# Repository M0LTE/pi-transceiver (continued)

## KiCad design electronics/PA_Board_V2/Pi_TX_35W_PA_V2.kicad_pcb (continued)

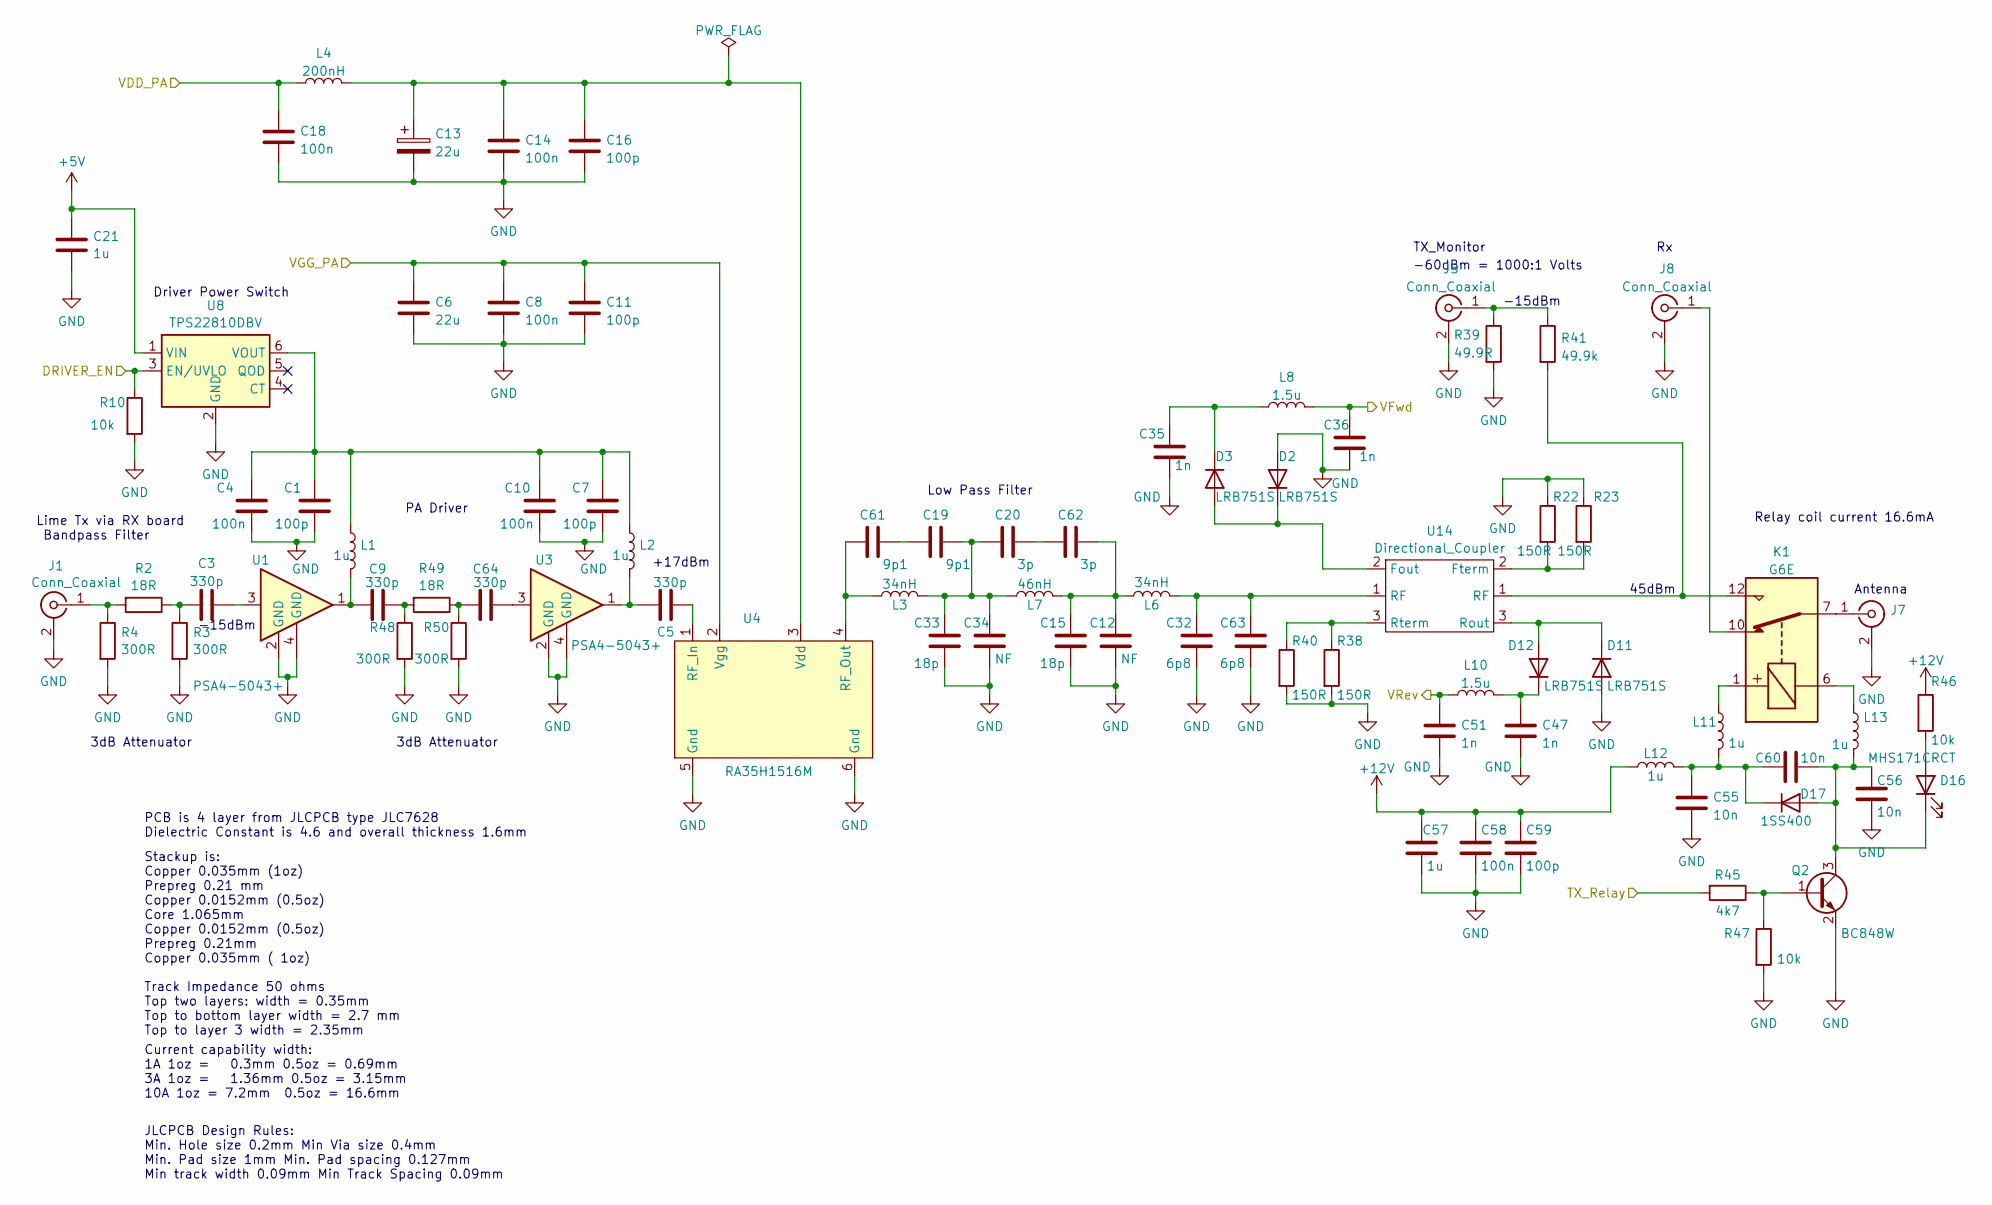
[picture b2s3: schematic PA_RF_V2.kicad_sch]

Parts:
C1, C7, C11, C16, C59: 100p; C_0603_1608Metric; LCSC Part C296046
C3, C5, C9, C64: 330p; C_0603_1608Metric; LCSC Part C458903
C4, C8, C10, C14, C18, C58: 100n; C_0603_1608Metric; LCSC Part C88136
C6: 22u; C_0805_2012Metric; LCSC Part C602037
C12, C34: NF; C_1206_3216Metric
C13: 22u; CP_EIA-7343-43_Kemet-X; LCSC Part C1956447
C15, C33: 18p; C_1206_3216Metric
C19, C61: 9p1; C_1206_3216Metric
C20, C62: 3p; C_1206_3216Metric
C21: 1u; C_0603_1608Metric; LCSC Part C88136
C32, C63: 6p8; C_1206_3216Metric
C35, C36, C47, C51: 1n; C_0603_1608Metric; LCSC Part C2839443
C55, C56, C60: 10n; C_0603_1608Metric; LCSC Part C2215227
C57: 1u; C_0603_1608Metric; LCSC Part C89376
D2, D3, D11, D12: LRB751S; D_SOD-523; LCSC Part C113407
D16: MHS171CRCT; MHS171; LCSC Part C693903
D17: 1SS400; D_SOD-523; LCSC Part C68951
J1, J5, J7, J8: Conn_Coaxial; SMA_Samtec_SMA-J-P-X-ST-EM1_EdgeMount; LCSC Part C496550
K1: G6E; Relay_SPDT_Omron_G6E; LCSC Part C1525391
L1, L2, L11, L12, L13: 1u; L_0805_2012Metric; LCSC Part C703134
L3, L6: 34nH; Wire_Inductor 12x8.5
L4: 200nH; L_1812_4532Metric; LCSC Part C2858475
L7: 46nH; Wire_Inductor 15.5x8.5
L8, L10: 1.5u; L_0805_2012Metric; LCSC Part C139220
Q2: BC848W; SOT-323_SC-70; LCSC Part C549496
R2, R49: 18R; R_0603_1608Metric; LCSC Part C245924
R3, R4, R48, R50: 300R; R_0603_1608Metric; LCSC Part C2930092
R10, R46, R47: 10k; R_0603_1608Metric; LCSC Part C25804
R22, R23, R38, R40: 150R; R_0603_1608Metric; LCSC Part C22808
R39: 49.9R; R_0603_1608Metric; LCSC Part C23185
R41: 49.9k; R_0603_1608Metric; LCSC Part C23184
R45: 4k7; R_0603_1608Metric; LCSC Part C23162
U1, U3: PSA4-5043+; SOT-343_SC-70-4; LCSC Part C5240848
U4: RA35H1516M; RF_PA_Module
U8: TPS22810DBV; SOT-23-6; LCSC Part C205990
U14: Directional_Coupler; Linear_Coupler

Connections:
+5V: C21.1, U8.1 (VIN); also elsewhere on the board
+12V: C57.1, C58.1, C59.1, L12.1, R46.1; also elsewhere on the board
/PA_Power/VDD_PA: C18.1, L4.1; also elsewhere on the board
/PA_Power/VGG_PA: C6.1, C8.1, C11.1, U4.2 (Vgg); also elsewhere on the board
/PA_Protection/DRIVER_EN: R10.1, U8.3 (EN/UVLO); also elsewhere on the board
/PA_Protection/TX_Relay: R45.2; also elsewhere on the board
/PA_Protection/VFwd: C36.1, L8.2; also elsewhere on the board
/PA_Protection/VRev: C51.1, L10.1; also elsewhere on the board
GND: C1.1, C4.1, C6.2, C7.1, C8.2, C10.1, C11.2, C12.2, C13.2, C14.2, C15.2, C16.2, C18.2, C21.2, C32.2, C33.2, C34.2, C35.2, C36.2, C47.2, C51.2, C55.2, C56.2, C57.2, C58.2, C59.2, C63.2, D2.2 (A), D11.2 (A), J1.2 (Ext), J5.2 (Ext), J7.2 (Ext), J8.2 (Ext), Q2.2 (E), R3.2, R4.2, R10.2, R22.1, R23.1, R38.2, R39.2, R40.2, R47.2, R48.2, R50.2, U1.2 (GND), U1.4 (GND), U3.2 (GND), U3.4 (GND), U4.5 (Gnd), U4.6 (Gnd), U8.2 (GND); also elsewhere on the board
unnamed: C3.1, U1.3
unnamed: C3.2, R2.1, R3.1
unnamed: C5.2, L2.2, U3.1
unnamed: C9.1, R48.1, R49.2
unnamed: C9.2, L1.2, U1.1
unnamed: C12.1, C15.1, C62.2, L6.1, L7.2
unnamed: C19.1, C61.2
unnamed: C19.2, C20.1, C33.1, C34.1, L3.2, L7.1
unnamed: C20.2, C62.1
unnamed: C64.1, U3.3
unnamed: C64.2, R49.1, R50.1
unnamed: C35.1, D3.1 (K), L8.1
unnamed: C47.1, D12.1 (K), L10.2
unnamed: D16.2 (A), R46.2
unnamed: C56.1, C60.1, D16.1 (K), D17.2 (A), L13.2, Q2.3 (C)
unnamed: C55.1, C60.2, D17.1 (K), L11.2, L12.2
unnamed: J1.1 (In), R2.2, R4.1
unnamed: J5.1 (In), R39.1, R41.1
unnamed: J7.1 (In), K1.7
unnamed: J8.1 (In), K1.10
unnamed: K1.1, L11.1
unnamed: K1.6, L13.1
unnamed: Q2.1 (B), R45.1, R47.1
unnamed: C5.1, U4.1 (RF_In)
unnamed: C61.1, L3.1, U4.4 (RF_Out)
unnamed: C13.1, C14.1, C16.1, L4.2, U4.3 (Vdd)
unnamed: C1.2, C4.2, C7.2, C10.2, L1.1, L2.1, U8.6 (VOUT)

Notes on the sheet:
3dB Attenuator
JLCPCB Design Rules: Min. Hole size 0.2mm Min Via size 0.4mm Min. Pad size 1mm Min. Pad spacing 0.127mm Min track width 0.09mm Min Track Spacing 0.09mm
Driver Power Switch
+17dBm
Stackup is: Copper 0.035mm (1oz) Prepreg 0.21 mm Copper 0.0152mm (0.5oz) Core 1.065mm Copper 0.0152mm (0.5oz) Prepreg 0.21mm Copper 0.035mm ( 1oz)
Current capability width: 1A 1oz = 0.3mm 0.5oz = 0.69mm 3A 1oz = 1.36mm 0.5oz = 3.15mm 10A 1oz = 7.2mm 0.5oz = 16.6mm
Antenna
TX_Monitor
45dBm
Lime Tx via RX board Bandpass Filter
-15dBm
Low Pass Filter
-60dBm = 1000:1 Volts
Track Impedance 50 ohms Top two layers: width = 0.35mm Top to bottom layer width = 2.7 mm Top to layer 3 width = 2.35mm
Relay coil current 16.6mA
PCB is 4 layer from JLCPCB type JLC7628 Dielectric Constant is 4.6 and overall thickness 1.6mm
PA Driver

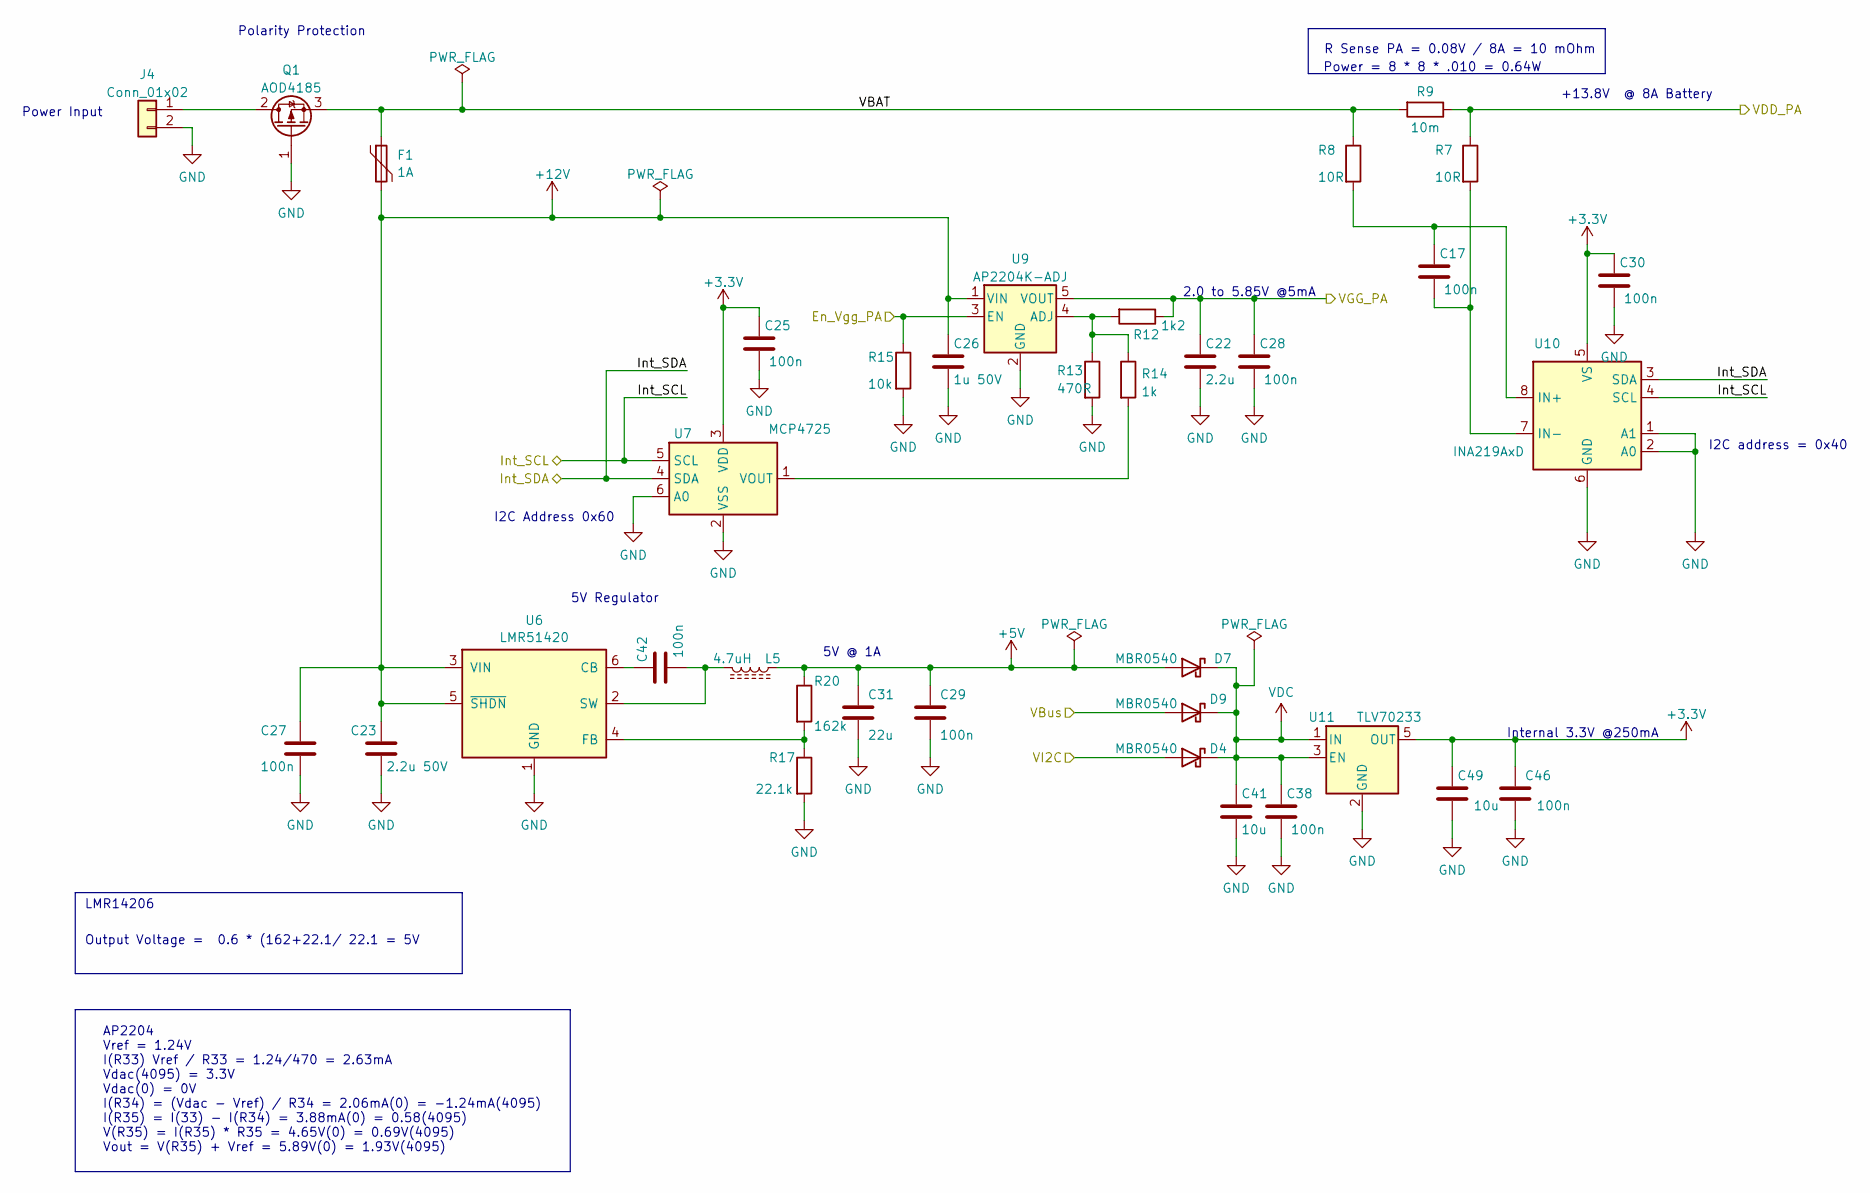
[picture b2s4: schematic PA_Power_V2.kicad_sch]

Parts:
C17, C25, C27, C28, C29, C30, C38, C42, C46: 100n; C_0603_1608Metric; LCSC Part C88136
C22: 2.2u; C_0603_1608Metric; LCSC Part C57895
C23: 2.2u 50V; C_0805_2012Metric; LCSC Part C377773
C26: 1u 50V; C_0603_1608Metric; LCSC Part C15849
C31: 22u; C_0805_2012Metric; LCSC Part C602037
C41, C49: 10u; C_0603_1608Metric; LCSC Part C96446
D4, D7, D9: MBR0540; D_SOD-123; LCSC Part C3018524
F1: 1A; Fuse_1206_3216Metric; LCSC Part C910830
J4: Conn_01x02; PhoenixContact_MSTBA_2,5_2-G_1x02_P5.00mm_Horizontal; LCSC Part C3697
L5: 4.7uH; L_7.3x7.3_H3.5; LCSC Part C76857
Q1: AOD4185; TO-252-2; LCSC Part C5261064
R7, R8: 10R; R_0603_1608Metric; LCSC Part C22859
R9: 10m; R_2816_7142Metric; LCSC Part C843884
R12: 1k2; R_0603_1608Metric; LCSC Part C22765
R13: 470R; R_0603_1608Metric; LCSC Part C23179
R14: 1k; R_0603_1608Metric; LCSC Part C21190
R15: 10k; R_0603_1608Metric; LCSC Part C25804
R17: 22.1k; R_0603_1608Metric; LCSC Part C25961
R20: 162k; R_0603_1608Metric; LCSC Part C3016073
U6: LMR51420; SOT-23-6; LCSC Part C5383002
U7: MCP4725; SOT-23-6; LCSC Part C144198
U9: AP2204K-ADJ; SOT-23-5; LCSC Part C264072
U10: INA219AxD; SOIC-8_3.9x4.9mm_P1.27mm; LCSC Part C138706
U11: TLV70233; SOT-23-5; LCSC Part C26833

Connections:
+3.3V: C25.1, C30.1, C46.1, C49.1, U7.3 (VDD), U10.5 (VS), U11.5 (OUT); also elsewhere on the board
+5V: C29.1, C31.1, D7.2 (A), L5.1, R20.1; also elsewhere on the board
+12V: C23.1, C26.1, C27.1, F1.2, U6.3 (VIN), U6.5 (~SHDN), U9.1 (VIN); also elsewhere on the board
/PA_Power/En_Vgg_PA: R15.1, U9.3 (EN); also elsewhere on the board
/PA_Power/Int_SCL: U7.5 (SCL), U10.4 (SCL); also elsewhere on the board
/PA_Power/Int_SDA: U7.4 (SDA), U10.3 (SDA); also elsewhere on the board
/PA_Power/VBAT: F1.1, Q1.3 (S), R8.1, R9.2
/PA_Power/VBus: D9.2 (A); also elsewhere on the board
/PA_Power/VDD_PA: R7.1, R9.1; also elsewhere on the board
/PA_Power/VGG_PA: C22.1, C28.1, R12.1, U9.5 (VOUT); also elsewhere on the board
/PA_Power/VI2C: D4.2 (A); also elsewhere on the board
GND: C22.2, C23.2, C25.2, C26.2, C27.2, C28.2, C29.2, C30.2, C31.2, C38.2, C41.2, C46.2, C49.2, J4.2, Q1.1 (G), R13.2, R15.2, R17.2, U6.1 (GND), U7.2 (VSS), U7.6 (A0), U9.2 (GND), U10.1 (A1), U10.2 (A0), U10.6 (GND), U11.2 (GND); also elsewhere on the board
unnamed: J4.1, Q1.2 (D)
unnamed: C42.1, U6.6 (CB)
unnamed: R17.1, R20.2, U6.4 (FB)
unnamed: C42.2, L5.2, U6.2 (SW)
unnamed: R14.2, U7.1 (VOUT)
unnamed: R12.2, R13.1, R14.1, U9.4 (ADJ)
unnamed: C17.1, R8.2, U10.8 (IN+)
unnamed: C17.2, R7.2, U10.7 (IN-)
VDC: C38.1, C41.1, D4.1 (K), D7.1 (K), D9.1 (K), U11.1 (IN), U11.3 (EN); also elsewhere on the board

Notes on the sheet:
5V @ 1A
Power Input
2.0 to 5.85V @5mA
I2C Address 0x60
+13.8V @ 8A Battery
I2C address = 0x40
LMR14206
Internal 3.3V @250mA
AP2204 Vref = 1.24V I(R33) Vref / R33 = 1.24/470 = 2.63mA Vdac(4095) = 3.3V Vdac(0) = 0V I(R34) = (Vdac - Vref) / R34 = 2.06mA(0) = -1.24mA(4095) I(R35) = I(33) - I(R34) = 3.88mA(0) = 0.58(4095) V(R35) = I(R35) * R35 = 4.65V(0) = 0.69V(4095) Vout = V(R35) + Vref = 5.89V(0) = 1.93V(4095)
R Sense PA = 0.08V / 8A = 10 mOhm
Polarity Protection
Power = 8 * 8 * .010 = 0.64W
Output Voltage = 0.6 * (162+22.1/ 22.1 = 5V
5V Regulator

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
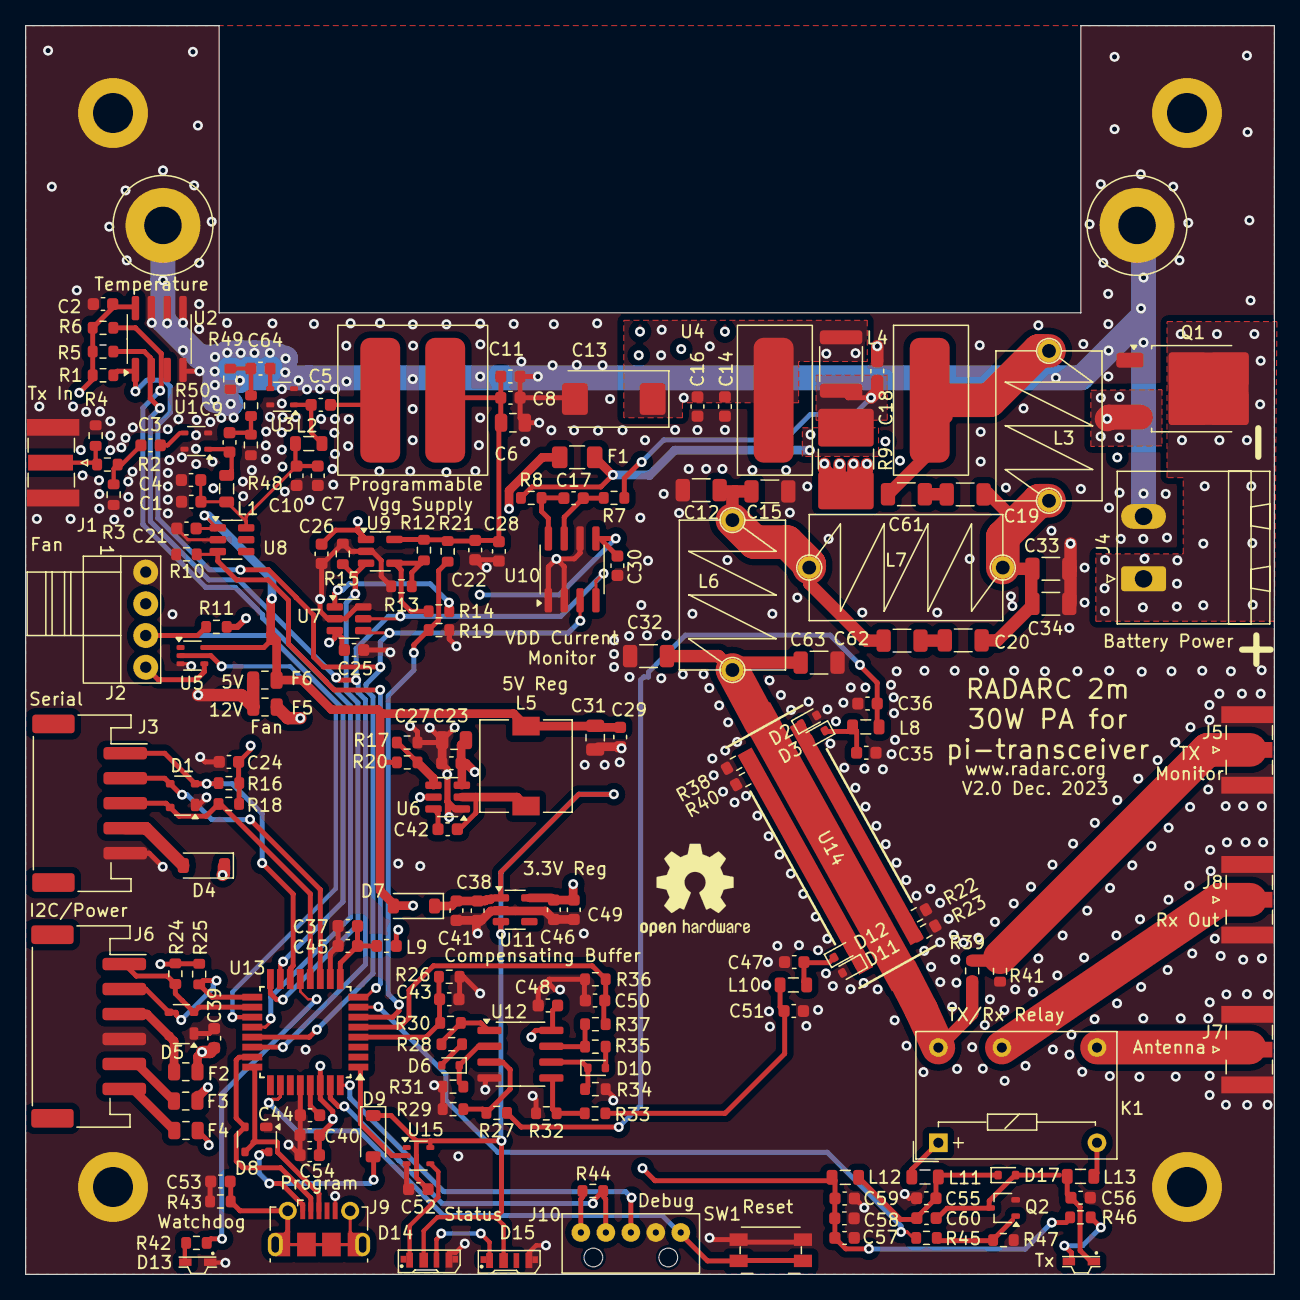
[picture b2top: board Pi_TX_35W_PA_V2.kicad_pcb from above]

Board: 4 copper layers, 100.0 x 100.0 mm, 185 parts (1 on the bottom side), 95 nets.

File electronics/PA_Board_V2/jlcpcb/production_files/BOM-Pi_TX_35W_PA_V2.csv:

Comment,Designator,Footprint,LCSC
LRB751S,"D11,D12,D2,D3",D_SOD-523,C113407
USB_B_Micro,J9,USB_Micro-B_Molex-105017-0001,C136000
INA219AxD,U10,SOIC-8_3.9x4.9mm_P1.27mm,C138706
1.5u,"L10,L8",L_0805_2012Metric,C139220
MCP4725,U7,SOT-23-6,C144198
G6E,K1,Relay_SPDT_Omron_G6E,C1525391
1u 50V,C26,C_0603_1608Metric,C15849
22u,C13,CP_EIA-7343-43_Kemet-X,C1956447
TPS22810DBV,U8,SOT-23-6,C205990
1k,"R14,R42,R44",R_0603_1608Metric,C21190
10n,"C55,C56,C60",C_0603_1608Metric,C2215227
1k2,R12,R_0603_1608Metric,C22765
150R,"R22,R23,R38,R40",R_0603_1608Metric,C22808
10R,"R7,R8",R_0603_1608Metric,C22859
1M,R43,R_0603_1608Metric,C22935
330R,"R30,R37",R_0603_1608Metric,C23138
4k7,"R1,R16,R18,R24,R25,R28,R35,R45,R5,R6",R_0603_1608Metric,C23162
470R,R13,R_0603_1608Metric,C23179
49.9k,R41,R_0603_1608Metric,C23184
49.9R,R39,R_0603_1608Metric,C23185
18R,"R2,R49",R_0603_1608Metric,C245924
100k,"R29,R31,R32,R34",R_0603_1608Metric,C25803
10k,"R10,R11,R15,R19,R26,R27,R33,R36,R46,R47",R_0603_1608Metric,C25804
47k,R21,R_0603_1608Metric,C25819
22.1k,R17,R_0603_1608Metric,C25961
AP2204K-ADJ,U9,SOT-23-5,C264072
SP0503BAHT,"D1,D5,D8",SOT-143,C2682275
TLV70233,U11,SOT-23-5,C26833
1n,"C35,C36,C43,C47,C50,C51",C_0603_1608Metric,C2839443
150mA,"F2,F3,F4",Fuse_0805_2012Metric,C2840556
200nH,L4,L_1812_4532Metric,C2858475
SK6812,"D14,D15",SK6812SIDE-A-RVS,C2890037
300R,"R3,R4,R48,R50",R_0603_1608Metric,C2930092
LM2904,U12,SOIC-8_3.9x4.9mm_P1.27mm,C2941725
100p,"C1,C11,C16,C59,C7",C_0603_1608Metric,C296046
162k,R20,R_0603_1608Metric,C3016073
MBR0540,"D4,D7,D9",D_SOD-123,C3018524
2.2u 50V,C23,C_0805_2012Metric,C377773
330p,"C3,C5,C64,C9",C_0603_1608Metric,C458903
Conn_Coaxial,"J1,J5,J7,J8",SMA_Samtec_SMA-J-P-X-ST-EM1_EdgeMount,C496550
74LV1T34,"U15,U5",SOT-353_SC-70-5,C5199768
PSA4-5043+,"U1,U3",MM1362 PSA4-5043+,C5240848
AOD4185,Q1,TO-252-2,C5261064
SW_Push,SW1,Panasonic_EVQPUK_EVQPUB,C526225
LMR51420,U6,SOT-23-6,C5383002
BC848W,Q2,SOT-323_SC-70,C549496
4n7,C53,C_0603_1608Metric,C576815
2.2u,C22,C_0603_1608Metric,C57895
22u,"C31,C6",C_0805_2012Metric,C602037
ATSAMD21E18A-A,U13,TQFP-32_7x7mm_P0.8mm,C618770
1SS400,"D10,D17,D6",D_SOD-523,C68951
MHS171CRCT,D16,MHS171,C693903
MHS171UBCT,D13,MHS171,C693906
1u,"L1,L11,L12,L13,L2",L_0805_2012Metric,C703134
LM75B,U2,SOIC-8_3.9x4.9mm_P1.27mm,C725792
Conn_01x05,J3,JST_PH_S5B-PH-SM4-TB_1x05-1MP_P2.00mm_Horizontal,C7429692
Conn_01x06,J6,JST_PH_S6B-PH-SM4-TB_1x06-1MP_P2.00mm_Horizontal,C7429693
4.7uH,L5,L_7.3x7.3_H3.5,C76857
10m,R9,R_2816_7142Metric,C843884
100n,"C10,C14,C17,C18,C2,C21,C24,C25,C27,C28,C29,C30,C38,C39,C4,C42,C45,C46,C48,C54,C58,C8",C_0603_1608Metric,C88136
1u,"C37,C40,C44,C52,C57",C_0603_1608Metric,C89376
1A,F1,Fuse_1206_3216Metric,C910830
10u,"C41,C49",C_0603_1608Metric,C96446
L_Ferrite,L9,L_0603_1608Metric,C98298

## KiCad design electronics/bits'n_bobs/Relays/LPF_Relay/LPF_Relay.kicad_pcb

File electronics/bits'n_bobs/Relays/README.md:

# Relays

A selection of Relay modules to test different options for the Tx/Rx relay for the Pi Transceiver

Relay Options are:

* G2RL Large through hole relay recommended by W6PQL
* HF3 Surface mount relay recommended by W6PQL
* EE2 Surface mount relay used in Lime RFE and IC-9700
* G6E Through hole relay used in Elecraft XV144

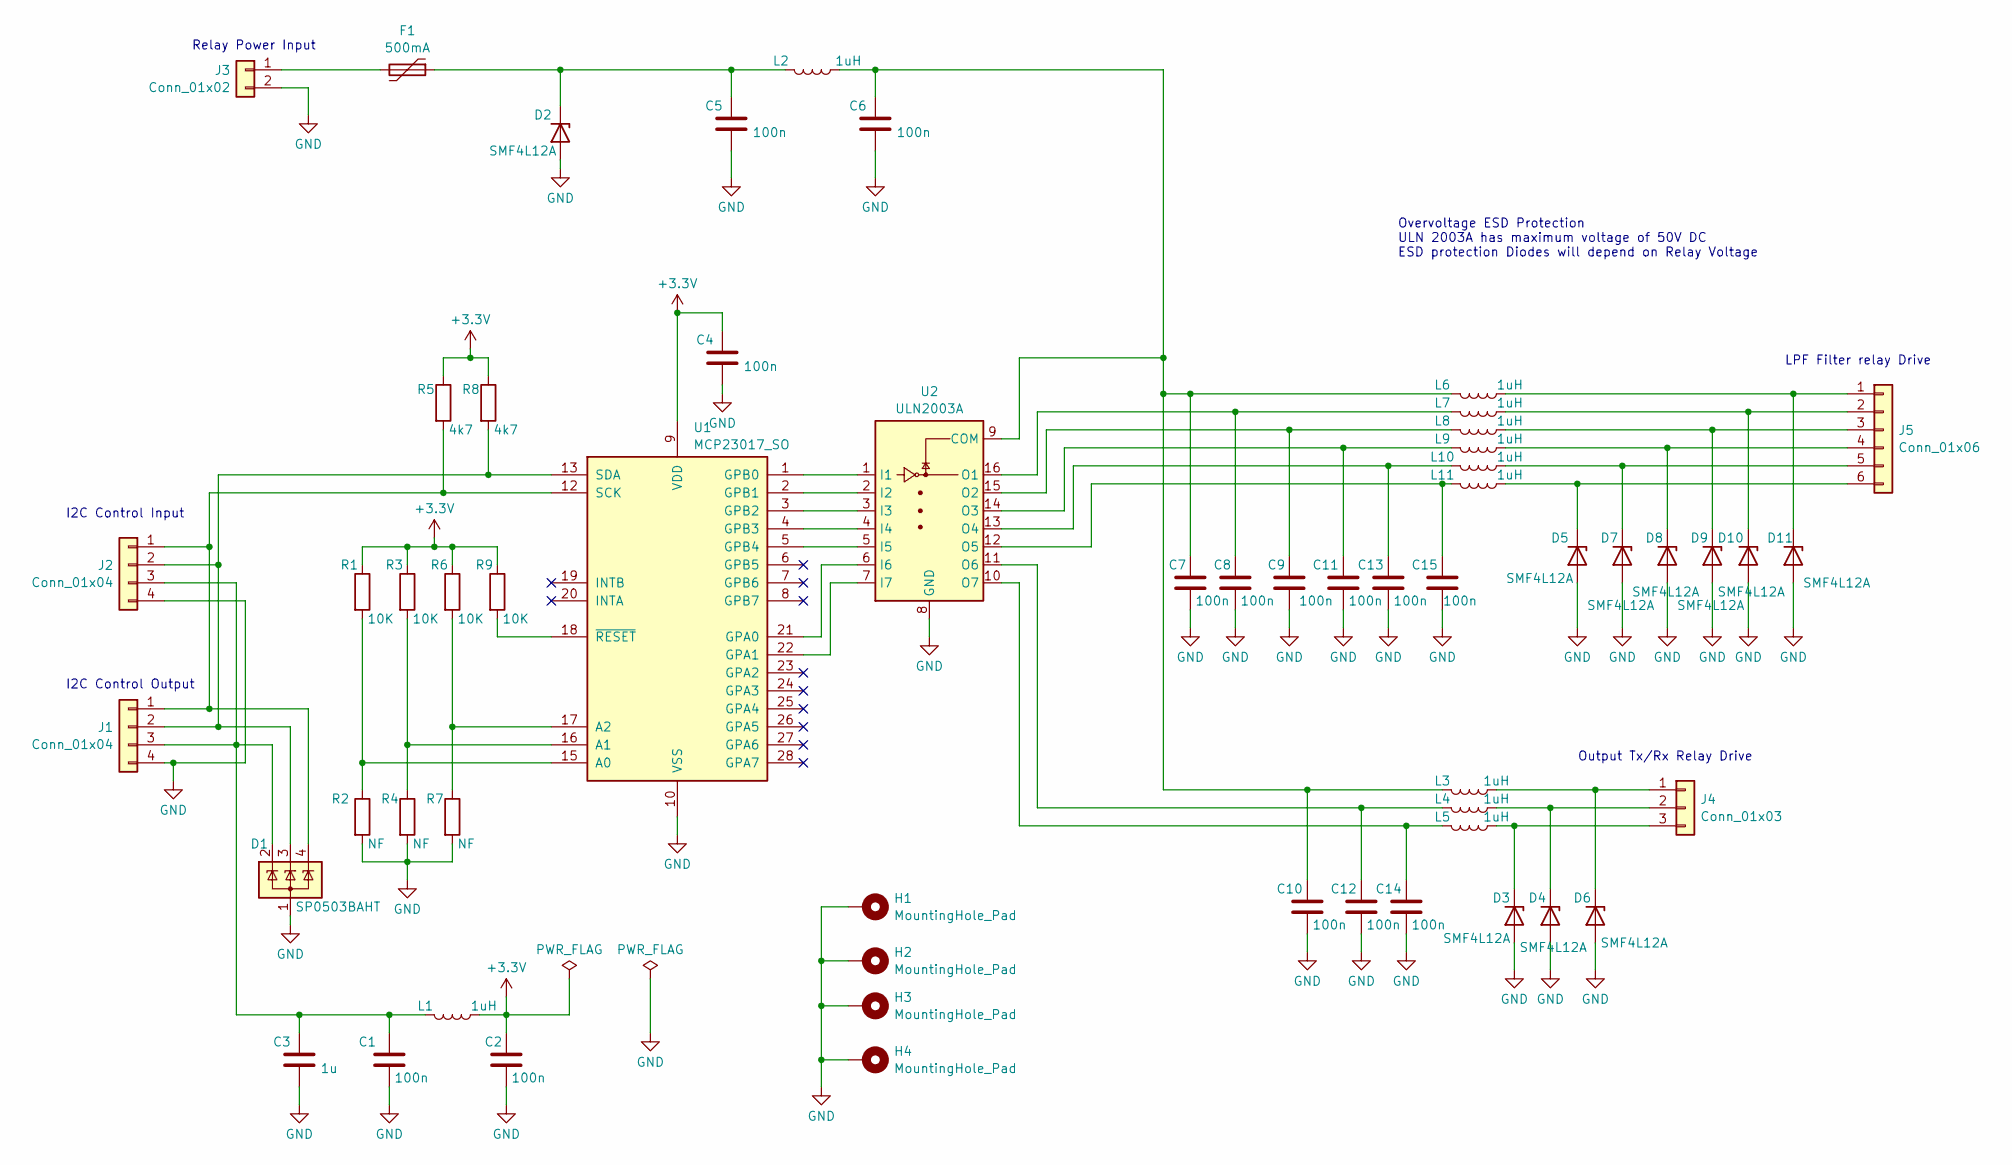
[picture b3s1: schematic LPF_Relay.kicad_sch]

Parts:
C1, C2, C4, C5, C6, C7, C8, C9, C10, C11, C12, C13, C14, C15: 100n; C_0603_1608Metric
C3: 1u; C_0603_1608Metric
D1: SP0503BAHT; SOT-143
D2, D3, D4, D5, D6, D7, D8, D9, D10, D11: SMF4L12A; D_SOD-123F
F1: 500mA; Fuse_Bourns_MF-SM_9.5x6.71mm
H1, H2, H3, H4: MountingHole_Pad; MountingHole_3.2mm_M3_DIN965_Pad
J1, J2: Conn_01x04; JST_PH_S4B-PH-SM4-TB_1x04-1MP_P2.00mm_Horizontal
J3: Conn_01x02; JST_XH_S2B-XH-A-1_1x02_P2.50mm_Horizontal
J4: Conn_01x03; JST_XH_S3B-XH-A-1_1x03_P2.50mm_Horizontal
J5: Conn_01x06; JST_XH_S6B-XH-A-1_1x06_P2.50mm_Horizontal
L1, L2, L3, L4, L5, L6, L7, L8, L9, L10, L11: 1uH; L_0603_1608Metric
R1, R3, R6, R9: 10K; R_0603_1608Metric
R2, R4, R7: NF; R_0603_1608Metric
R5, R8: 4k7; R_0603_1608Metric
U1: MCP23017_SO; SSOP-28_5.3x10.2mm_P0.65mm
U2: ULN2003A; SO-16_3.9x9.9mm_P1.27mm

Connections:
+3.3V: C2.1, C4.1, L1.1, R1.1, R3.1, R5.1, R6.1, R8.1, R9.1, U1.9 (VDD)
GND: C1.2, C2.2, C3.2, C4.2, C5.2, C6.2, C7.2, C8.2, C9.2, C10.2, C11.2, C12.2, C13.2, C14.2, C15.2, D1.1 (A), D2.2 (A), D3.2 (A), D4.2 (A), D5.2 (A), D6.2 (A), D7.2 (A), D8.2 (A), D9.2 (A), D10.2 (A), D11.2 (A), H1.1, H2.1, H3.1, H4.1, J1.4, J2.4, J3.2, R2.2, R4.2, R7.2, U1.10 (VSS), U2.8 (GND)
unnamed: C5.1, D2.1 (K), F1.1, L2.2
unnamed: D3.1 (K), J4.3, L5.1
unnamed: D4.1 (K), J4.2, L4.1
unnamed: D5.1 (K), J5.6, L11.1
unnamed: D6.1 (K), J4.1, L3.1
unnamed: D7.1 (K), J5.5, L10.1
unnamed: D8.1 (K), J5.4, L9.1
unnamed: D9.1 (K), J5.3, L8.1
unnamed: D10.1 (K), J5.2, L7.1
unnamed: D11.1 (K), J5.1, L6.1
unnamed: D1.4 (K), J1.1, J2.1, R5.2, U1.12 (SCK)
unnamed: D1.3 (K), J1.2, J2.2, R8.2, U1.13 (SDA)
unnamed: C1.1, C3.1, D1.2 (K), J1.3, J2.3, L1.2
unnamed: F1.2, J3.1
unnamed: R1.2, R2.1, U1.15 (A0)
unnamed: R3.2, R4.1, U1.16 (A1)
unnamed: R6.2, R7.1, U1.17 (A2)
unnamed: U1.21 (GPA0), U2.6 (I6)
unnamed: U1.22 (GPA1), U2.7 (I7)
unnamed: U1.1 (GPB0), U2.1 (I1)
unnamed: U1.2 (GPB1), U2.2 (I2)
unnamed: U1.3 (GPB2), U2.3 (I3)
unnamed: U1.4 (GPB3), U2.4 (I4)
unnamed: U1.5 (GPB4), U2.5 (I5)
unnamed: R9.2, U1.18 (~RESET)
unnamed: C6.1, C7.1, C10.1, L2.1, L3.2, L6.2, U2.9 (COM)
unnamed: C8.1, L7.2, U2.16 (O1)
unnamed: C9.1, L8.2, U2.15 (O2)
unnamed: C11.1, L9.2, U2.14 (O3)
unnamed: C13.1, L10.2, U2.13 (O4)
unnamed: C15.1, L11.2, U2.12 (O5)
unnamed: C12.1, L4.2, U2.11 (O6)
unnamed: C14.1, L5.2, U2.10 (O7)

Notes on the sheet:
I2C Control Output
LPF Filter relay Drive
Output Tx/Rx Relay Drive
I2C Control Input
Relay Power Input
Overvoltage ESD Protection ULN 2003A has maximum voltage of 50V DC ESD protection Diodes will depend on Relay Voltage

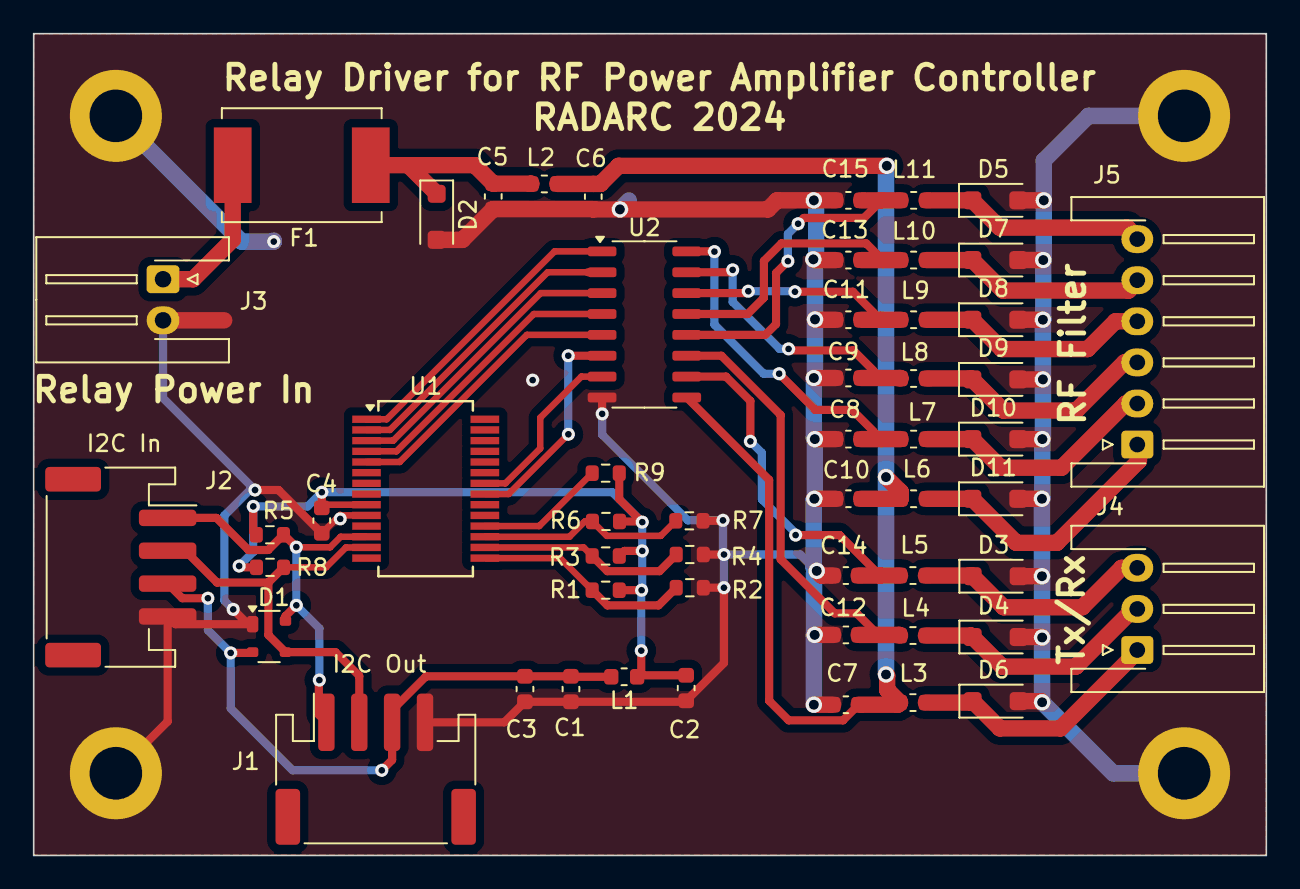
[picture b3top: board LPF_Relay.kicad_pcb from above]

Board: 2 copper layers, 75.0 x 50.0 mm, 58 parts (0 on the bottom side), 35 nets.

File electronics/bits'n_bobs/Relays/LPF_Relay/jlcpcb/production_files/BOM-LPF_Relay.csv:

Comment,Designator,Footprint,LCSC
1uH,L1,L_0603_1608Metric,
Conn_01x06,J5,JST_XH_S6B-XH-A-1_1x06_P2.50mm_Horizontal,
100n,C15,C_0603_1608Metric,
SMF4L12A,D9,D_SOD-123F,
Conn_01x04,J2,JST_PH_S4B-PH-SM4-TB_1x04-1MP_P2.00mm_Horizontal,
SMF4L12A,D5,D_SOD-123F,
SMF4L12A,D11,D_SOD-123F,
100n,C14,C_0603_1608Metric,
ULN2003A,U2,SO-16_3.9x9.9mm_P1.27mm,
MountingHole_Pad,H1,MountingHole_3.2mm_M3_DIN965_Pad,
10K,R6,R_0603_1608Metric,
100n,C1,C_0603_1608Metric,
10K,R3,R_0603_1608Metric,
1uH,L5,L_0603_1608Metric,
SMF4L12A,D6,D_SOD-123F,
1u,C3,C_0603_1608Metric,
100n,C11,C_0603_1608Metric,
MountingHole_Pad,H2,MountingHole_3.2mm_M3_DIN965_Pad,
Conn_01x03,J4,JST_XH_S3B-XH-A-1_1x03_P2.50mm_Horizontal,
100n,C2,C_0603_1608Metric,
10K,R9,R_0603_1608Metric,
SP0503BAHT,D1,SOT-143,
100n,C6,C_0603_1608Metric,
1uH,L3,L_0603_1608Metric,
4k7,R5,R_0603_1608Metric,
1uH,L2,L_0603_1608Metric,
100n,C13,C_0603_1608Metric,
100n,C4,C_0603_1608Metric,
100n,C9,C_0603_1608Metric,
1uH,L10,L_0603_1608Metric,
MCP23017_SO,U1,SSOP-28_5.3x10.2mm_P0.65mm,
Conn_01x02,J3,JST_XH_S2B-XH-A-1_1x02_P2.50mm_Horizontal,
1uH,L4,L_0603_1608Metric,
100n,C7,C_0603_1608Metric,
100n,C8,C_0603_1608Metric,
NF,R4,R_0603_1608Metric,
NF,R2,R_0603_1608Metric,
SMF4L12A,D4,D_SOD-123F,
1uH,L11,L_0603_1608Metric,
100n,C12,C_0603_1608Metric,
1uH,L9,L_0603_1608Metric,
SMF4L12A,D8,D_SOD-123F,
4k7,R8,R_0603_1608Metric,
10K,R1,R_0603_1608Metric,
MountingHole_Pad,H4,MountingHole_3.2mm_M3_DIN965_Pad,
Conn_01x04,J1,JST_PH_S4B-PH-SM4-TB_1x04-1MP_P2.00mm_Horizontal,
1uH,L6,L_0603_1608Metric,
MountingHole_Pad,H3,MountingHole_3.2mm_M3_DIN965_Pad,
1uH,L8,L_0603_1608Metric,
SMF4L12A,D7,D_SOD-123F,
100n,C5,C_0603_1608Metric,
100n,C10,C_0603_1608Metric,
SMF4L12A,D3,D_SOD-123F,
NF,R7,R_0603_1608Metric,
SMF4L12A,D10,D_SOD-123F,
SMF4L12A,D2,D_SOD-123F,
1uH,L7,L_0603_1608Metric,
 500mA,F1,Fuse_0805_2012Metric,
